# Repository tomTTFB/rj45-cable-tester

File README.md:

# RJ45 Cable Tester

A small board that tests ethernet cables. Plug both ends in and 8 LEDs show if each wire is working, broken, shorted or swapped.

   Made for the [Hack Club 8-Pin Grant](https://8-pin-grant.hackclub.com/)

## How It Works

- Plug one end of a cable into A and the other into B
- Tests run continuously, the LEDs update a few times a second
- The ATtiny412 drives each wire one at a time through the MCP23017 (I2C expander)
- It reads which pins come through on the other end
- J2 pin 8 is read directly by the ATtiny on PA7 because MCP23017 GPA7/GPB7 are output-only on newer chips
- The 8 LEDs show what each wire is doing

## LED Key

- Green: ok
- Red: open (broken wire)
- Yellow: short
- Blue: swapped
- Purple: crossover cable

## Parts

Full list with part numbers in the [BOM](rj45-tester/rj45-tester.csv)

- ATtiny412 (SOIC-8)
- MCP23017 I2C expander (DIP-28)
- 8x WS2812B-style LEDs (Inolux IN-PI55TATPRPGPB)
- 2x Amphenol RJ45 jacks
- USB-C (power only)

## Headers

- J1 UPDI: GND, 5V, UPDI (for programming)
- J4 serial: TX, GND, 5V

## Files

- rj45-tester/: KiCad project
- JOURNAL.md: build log

## Current Project Status

- PCB designed, DRC passed and waiting for review
- Firmware not written yet

## Warning

No PoE or live network ports, only plug in cables

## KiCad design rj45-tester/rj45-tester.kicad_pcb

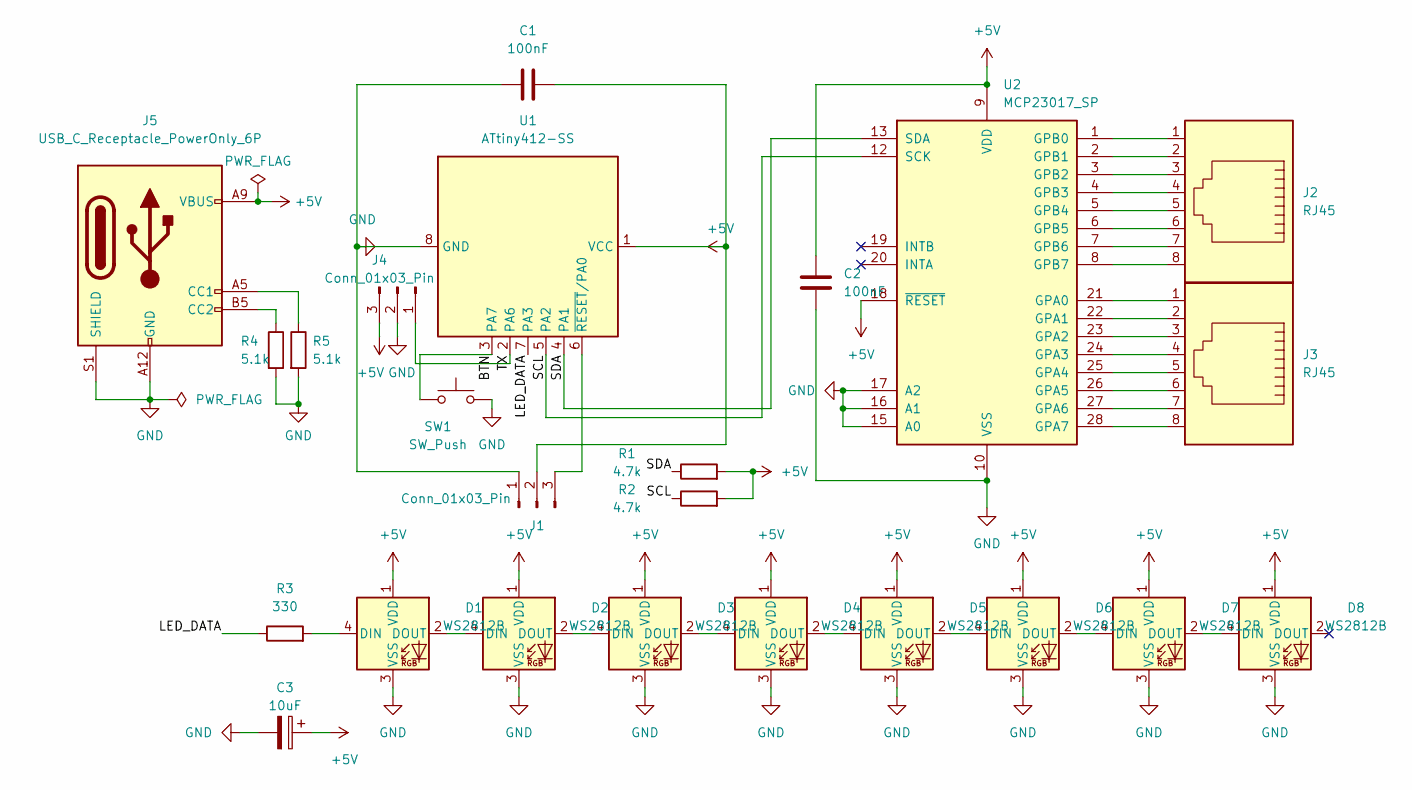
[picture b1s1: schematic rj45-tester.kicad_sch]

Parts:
C1, C2: 100nF; C_Disc_D5.1mm_W3.2mm_P5.00mm; Part Number K104M20X7RH53H5
C3: 10uF; CP_Radial_D5.0mm_P2.00mm; Part Number ESC106M063AC3AA
D1, D2, D3, D4, D5, D6, D7, D8: WS2812B; LED_WS2812B_PLCC4_5.0x5.0mm_P3.2mm; Part Number IN-PI55TATPRPGPB
J1, J4: Conn_01x03_Pin; PinHeader_1x03_P2.54mm_Vertical; Part Number G800LR305018EU
J2, J3: RJ45; RJ45_Amphenol_54602-x08_Horizontal; Part Number 54602-908LF
J5: USB_C_Receptacle_PowerOnly_6P; USB_C_Receptacle_GCT_USB4125-xx-x_6P_TopMnt_Horizontal; Part Number USB4125-GF-A
R1, R2: 4.7k; R_Axial_DIN0207_L6.3mm_D2.5mm_P10.16mm_Horizontal; Part Number MFR-25FBF52-4K7
R3: 330; R_Axial_DIN0207_L6.3mm_D2.5mm_P10.16mm_Horizontal; Part Number MFR-25FBF52-330R
R4, R5: 5.1k; R_Axial_DIN0207_L6.3mm_D2.5mm_P10.16mm_Horizontal; Part Number MFR-25FBF52-5K1
SW1: SW_Push; SW_PUSH_6mm; Part Number B3W-1002
U1: ATtiny412-SS; SOIC-8_3.9x4.9mm_P1.27mm; Part Number ATTINY412-SSN
U2: MCP23017_SP; DIP-28_W7.62mm; Part Number MCP23017-E/SP

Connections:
+5V: C1.2, C2.1, C3.1, D1.1 (VDD), D2.1 (VDD), D3.1 (VDD), D4.1 (VDD), D5.1 (VDD), D6.1 (VDD), D7.1 (VDD), D8.1 (VDD), J1.2, J4.3, J5.A9 (VBUS), J5.B9 (VBUS), R1.2, R2.2, U1.1 (VCC), U2.9 (VDD), U2.18 (~RESET)
/LED_DATA: R3.1, U1.7 (PA3)
/SCL: R2.1, U1.5 (PA2), U2.12 (SCK)
/SDA: R1.1, U1.4 (PA1), U2.13 (SDA)
/TX: J4.1, U1.2 (PA6)
GND: C1.1, C2.2, C3.2, D1.3 (VSS), D2.3 (VSS), D3.3 (VSS), D4.3 (VSS), D5.3 (VSS), D6.3 (VSS), D7.3 (VSS), D8.3 (VSS), J1.1, J4.2, J5.A12 (GND), J5.B12 (GND), J5.S1 (SHIELD), R4.2, R5.2, SW1.2, U1.8 (GND), U2.10 (VSS), U2.15 (A0), U2.16 (A1), U2.17 (A2)
unnamed: D1.4 (DIN), R3.2
unnamed: D1.2 (DOUT), D2.4 (DIN)
unnamed: D2.2 (DOUT), D3.4 (DIN)
unnamed: D3.2 (DOUT), D4.4 (DIN)
unnamed: D4.2 (DOUT), D5.4 (DIN)
unnamed: D5.2 (DOUT), D6.4 (DIN)
unnamed: D6.2 (DOUT), D7.4 (DIN)
unnamed: D7.2 (DOUT), D8.4 (DIN)
unnamed: J1.3, U1.6 (~RESET/PA0)
unnamed: J5.A5 (CC1), R5.1
unnamed: J5.B5 (CC2), R4.1
unnamed: J3.1, U2.21 (GPA0)
unnamed: J3.2, U2.22 (GPA1)
unnamed: J3.3, U2.23 (GPA2)
unnamed: J3.4, U2.24 (GPA3)
unnamed: J3.5, U2.25 (GPA4)
unnamed: J3.6, U2.26 (GPA5)
unnamed: J3.7, U2.27 (GPA6)
unnamed: J3.8, U2.28 (GPA7)
unnamed: J2.1, U2.1 (GPB0)
unnamed: J2.2, U2.2 (GPB1)
unnamed: J2.3, U2.3 (GPB2)
unnamed: J2.4, U2.4 (GPB3)
unnamed: J2.5, U2.5 (GPB4)
unnamed: J2.6, U2.6 (GPB5)
unnamed: J2.7, U2.7 (GPB6)

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
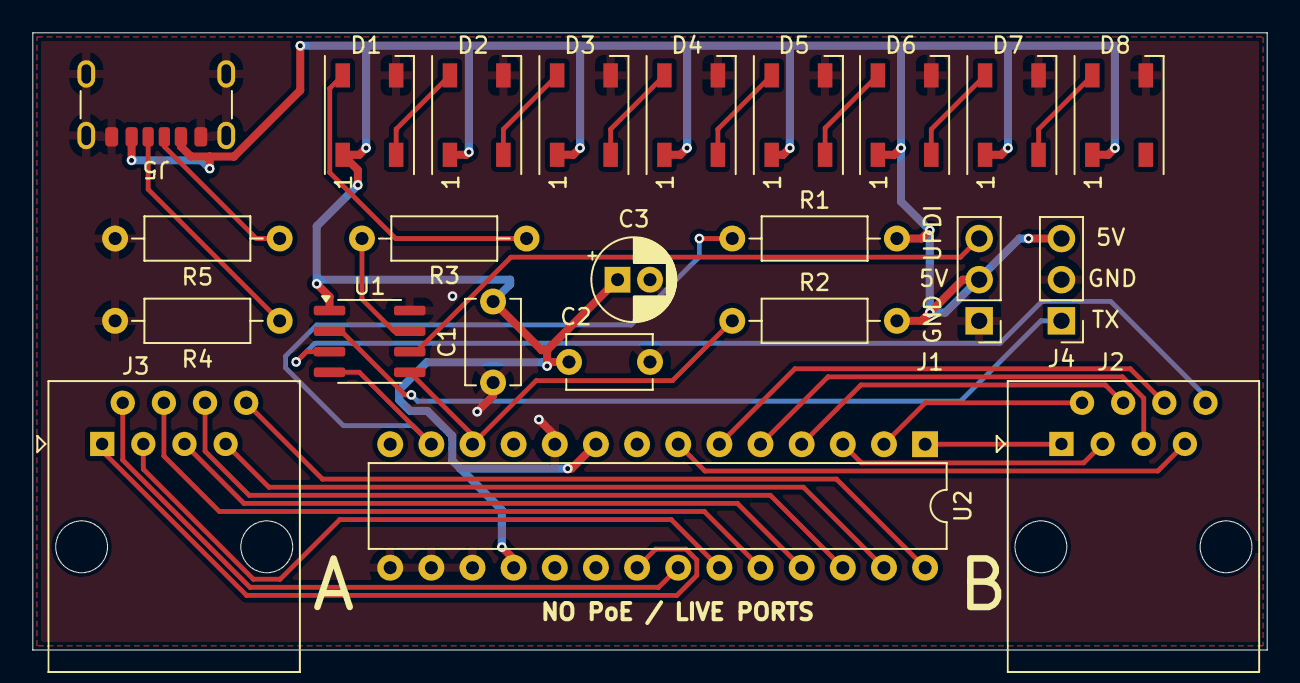
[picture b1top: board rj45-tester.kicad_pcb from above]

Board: 2 copper layers, 76.2 x 38.1 mm, 24 parts (1 on the bottom side), 33 nets.

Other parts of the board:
LOGO: LOGO
